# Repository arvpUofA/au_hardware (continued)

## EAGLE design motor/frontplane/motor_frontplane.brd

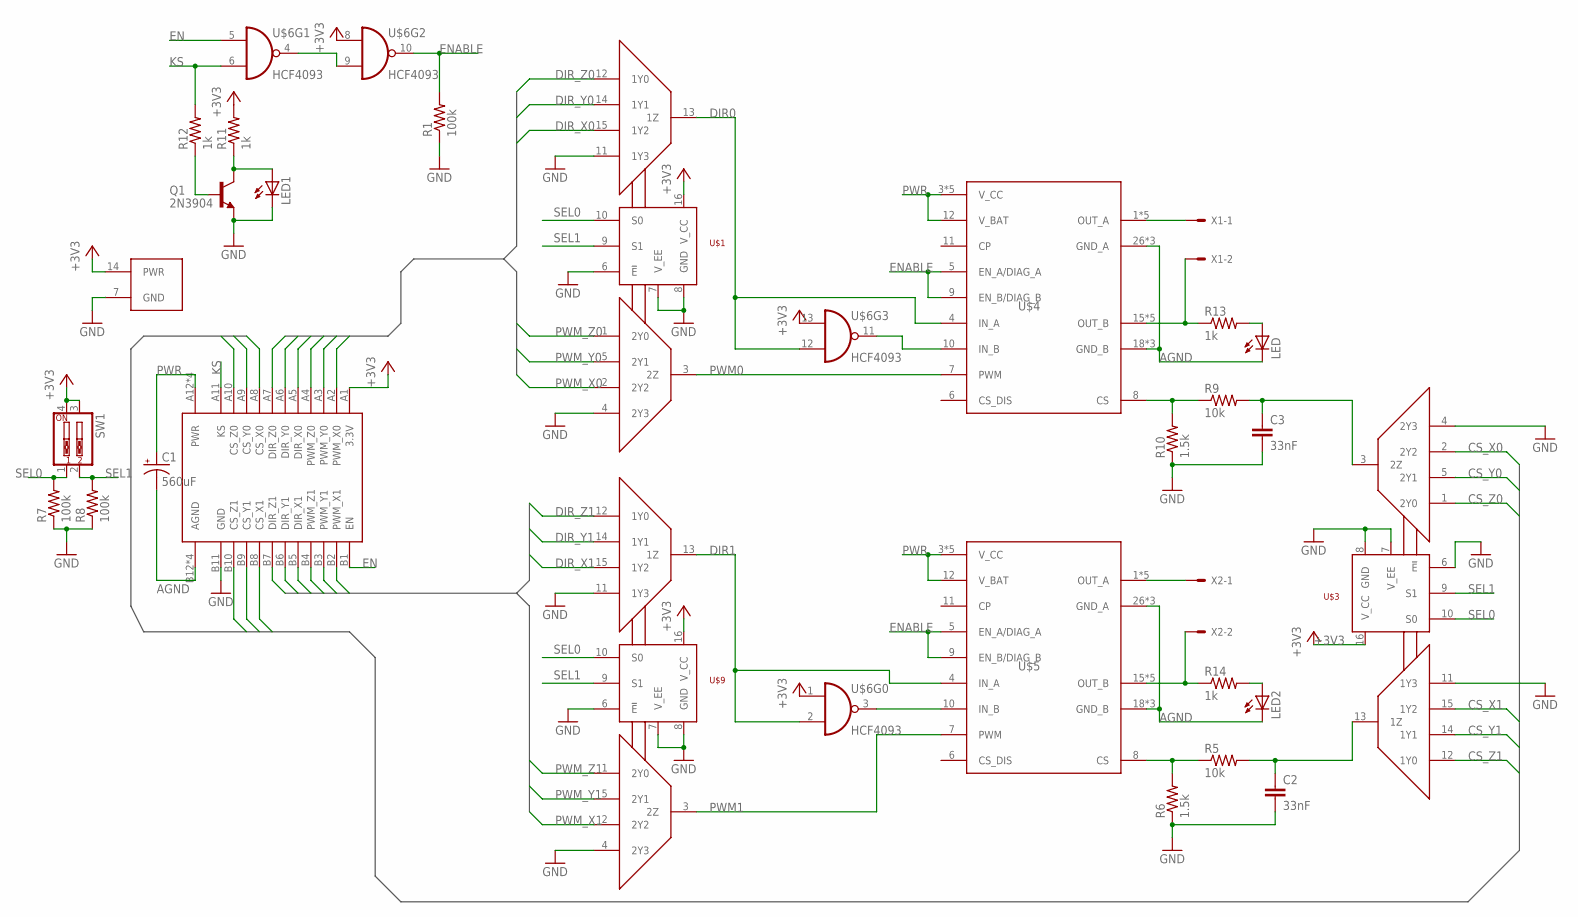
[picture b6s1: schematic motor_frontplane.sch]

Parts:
C1: 560uF; E3,5-10
C2, C3: 33nF; C2.5-2
LED, LED1, LED2: LED5MM
Q1: 2N3904; TO92
R1, R7, R8: 100k; R0805
R5, R9: 10k; R0805
R6, R10: 1.5k; R0805
R11, R12, R13, R14: 1k; R0805
SW1: SW_DIP-2; EDG-02
U$1, U$3, U$9: 74HC4052-Q100; SO16
U$2: MOTOR_BOARD_CONN; CARD_30PIN_8PWR
U$4, U$5: VNH5019A-E; MULTIPOWERSO-30
U$6: HCF4093; SO14
X1, X2: KK-156-2

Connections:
!DIR0: U$4.10 (IN_B), U$6.11 (O)
!DIR1: U$5.10 (IN_B), U$6.3 (O)
+3V3: R11.2, SW1.3, SW1.4, U$1.16 (V_CC), U$2.A1 (3.3V), U$3.16 (V_CC), U$6.1 (I0), U$6.8 (I0), U$6.13 (I0), U$6.14 (PWR), U$9.16 (V_CC)
AGND: C1.-, LED.K (C), LED2.K (C), U$2.B12 (AGND), U$2.B13 (AGND), U$2.B14 (AGND), U$2.B15 (AGND), U$4.18 (GND_B), U$4.19 (GND_B), U$4.20 (GND_B), U$4.26 (GND_A), U$4.27 (GND_A), U$4.28 (GND_A), U$5.18 (GND_B), U$5.19 (GND_B), U$5.20 (GND_B), U$5.26 (GND_A), U$5.27 (GND_A), U$5.28 (GND_A)
CS0: R9.1, R10.2, U$4.8 (CS)
CS1: R5.1, R6.2, U$5.8 (CS)
CS_X0: U$2.A8 (CS_X0), U$3.2 (2Y2)
CS_X1: U$2.B8 (CS_X1), U$3.15 (1Y2)
CS_Y0: U$2.A9 (CS_Y0), U$3.5 (2Y1)
CS_Y1: U$2.B9 (CS_Y1), U$3.14 (1Y1)
CS_Z0: U$2.A10 (CS_Z0), U$3.1 (2Y0)
CS_Z1: U$2.B10 (CS_Z1), U$3.12 (1Y0)
DIR0: U$1.13 (1Z), U$4.4 (IN_A), U$6.12 (I1)
DIR1: U$5.4 (IN_A), U$6.2 (I1), U$9.13 (1Z)
DIR_X0: U$1.15 (1Y2), U$2.A5 (DIR_X0)
DIR_X1: U$2.B5 (DIR_X1), U$9.15 (1Y2)
DIR_Y0: U$1.14 (1Y1), U$2.A6 (DIR_Y0)
DIR_Y1: U$2.B6 (DIR_Y1), U$9.14 (1Y1)
DIR_Z0: U$1.12 (1Y0), U$2.A7 (DIR_Z0)
DIR_Z1: U$2.B7 (DIR_Z1), U$9.12 (1Y0)
EN: U$2.B1 (EN), U$6.5 (I0)
ENABLE: R1.2, U$4.5 (EN_A/DIAG_A), U$4.9 (EN_B/DIAG_B), U$5.5 (EN_A/DIAG_A), U$5.9 (EN_B/DIAG_B), U$6.10 (O)
GND: C2.2, C3.2, LED1.K (C), Q1.3 (E), R1.1, R6.1, R7.1, R8.1, R10.1, U$1.4 (2Y3), U$1.6 (!E), U$1.7 (V_EE), U$1.8 (GND), U$1.11 (1Y3), U$2.B11 (GND), U$3.4 (2Y3), U$3.6 (!E), U$3.7 (V_EE), U$3.8 (GND), U$3.11 (1Y3), U$6.7 (GND), U$9.4 (2Y3), U$9.6 (!E), U$9.7 (V_EE), U$9.8 (GND), U$9.11 (1Y3)
KS: R12.2, U$2.A11 (KS), U$6.6 (I1)
unnamed: U$6.4 (O), U$6.9 (I1)
unnamed: C2.1, R5.2, U$3.13 (1Z)
unnamed: LED2.A, R14.2
unnamed: C3.1, R9.2, U$3.3 (2Z)
unnamed: LED1.A, Q1.1 (C), R11.1
unnamed: Q1.2 (B), R12.1
unnamed: LED.A, R13.2
OUT_A0: U$4.1 (OUT_A), U$4.25 (OUT_A), U$4.30 (OUT_A), U$4.OUTA (OUT_A), U$4.OUTA@1 (OUT_A), X1.1
OUT_A1: U$5.1 (OUT_A), U$5.25 (OUT_A), U$5.30 (OUT_A), U$5.OUTA (OUT_A), U$5.OUTA@1 (OUT_A), X2.1
OUT_B0: R13.1, U$4.15 (OUT_B), U$4.16 (OUT_B), U$4.21 (OUT_B), U$4.OUTB (OUT_B), U$4.OUTB@1 (OUT_B), X1.2
OUT_B1: R14.1, U$5.15 (OUT_B), U$5.16 (OUT_B), U$5.21 (OUT_B), U$5.OUTB (OUT_B), U$5.OUTB@1 (OUT_B), X2.2
PWM0: U$1.3 (2Z), U$4.7 (PWM)
PWM1: U$5.7 (PWM), U$9.3 (2Z)
PWM_X0: U$1.2 (2Y2), U$2.A2 (PWM_X0)
PWM_X1: U$2.B2 (PWM_X1), U$9.2 (2Y2)
PWM_Y0: U$1.5 (2Y1), U$2.A3 (PWM_Y0)
PWM_Y1: U$2.B3 (PWM_Y1), U$9.5 (2Y1)
PWM_Z0: U$1.1 (2Y0), U$2.A4 (PWM_Z0)
PWM_Z1: U$2.B4 (PWM_Z1), U$9.1 (2Y0)
PWR: C1.+, U$2.A12 (PWR), U$2.A13 (PWR), U$2.A14 (PWR), U$2.A15 (PWR), U$4.3 (V_CC), U$4.12 (V_BAT), U$4.13 (V_CC), U$4.23 (V_CC), U$4.VCC (V_CC), U$4.VCC@1 (V_CC), U$5.3 (V_CC), U$5.12 (V_BAT), U$5.13 (V_CC), U$5.23 (V_CC), U$5.VCC (V_CC), U$5.VCC@1 (V_CC)
SEL0: R7.2, SW1.1, U$1.10 (S0), U$3.10 (S0), U$9.10 (S0)
SEL1: R8.2, SW1.2, U$1.9 (S1), U$3.9 (S1), U$9.9 (S1)

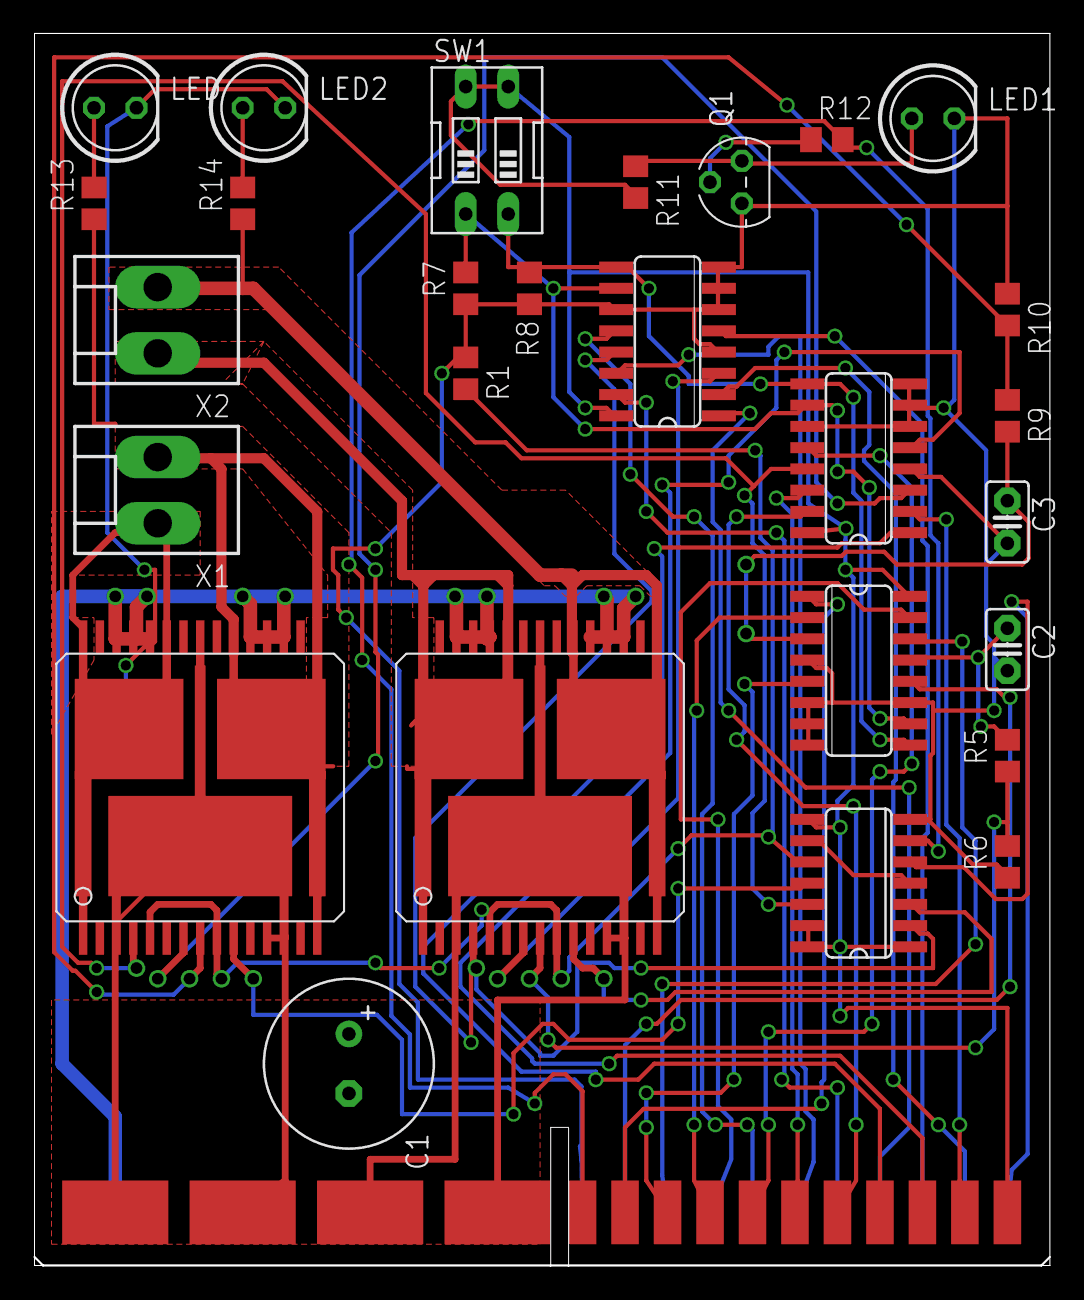
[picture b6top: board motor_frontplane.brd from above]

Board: 2 copper layers, 60.7 x 73.7 mm, 28 parts (0 on the bottom side), 46 nets.
